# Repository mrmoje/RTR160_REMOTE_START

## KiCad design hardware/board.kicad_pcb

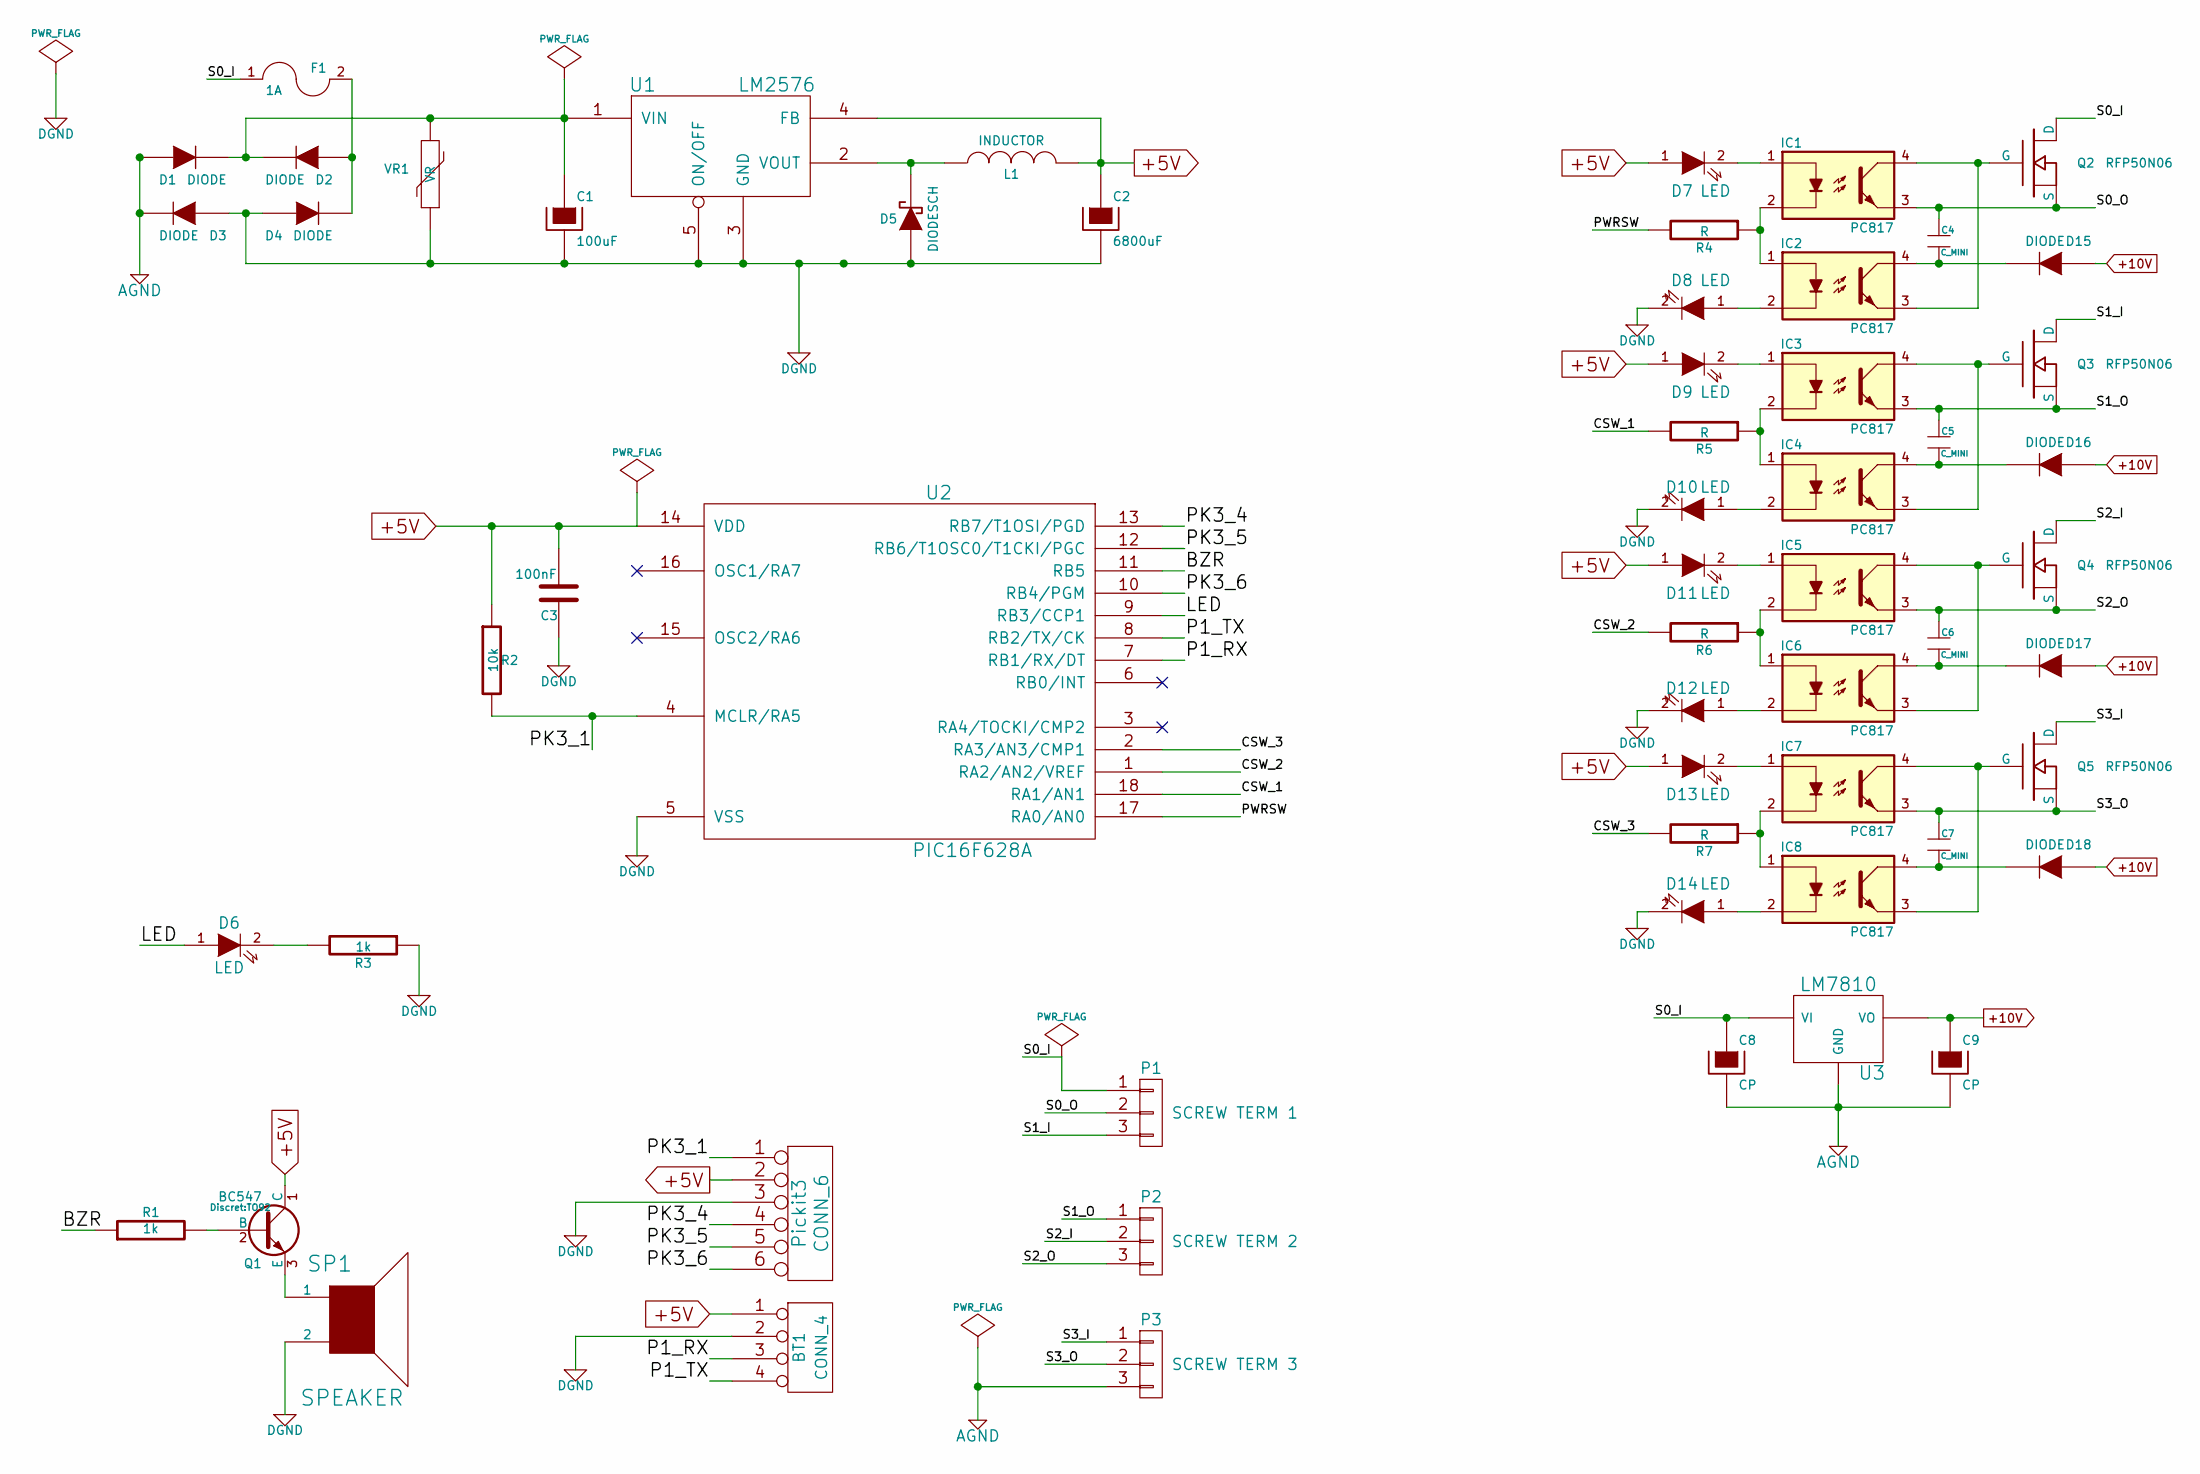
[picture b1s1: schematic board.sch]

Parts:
BT1: CONN_4; Pin_Header_Straight_1x04
C1: 100uF; Capacitor10x25RM2.5
C2: 6800uF; Capacitor16x25RM7.5
C3: 100nF; Capacitor7.5MMDiscRM5
C4, C5, C6, C7: C_MINI; Capacitor5x11RM2.5
C8, C9: CP; Capacitor8x13RM3.8
D1, D2, D3, D4, D15, D16, D17, D18: DIODE; Diode_DO-35_SOD27_Horizontal_RM10
D5: DIODESCH; Diode_DO-35_SOD27_Horizontal_RM10
D6, D7, D8, D9, D10, D11, D12, D13, D14: LED; LED-5MM
F1: 1A; Fuseholder5x20_horiz_SemiClosed_Casing10x25mm
IC1, IC2, IC3, IC4, IC5, IC6, IC7, IC8: PC817; DIP-4__300
L1: INDUCTOR; INDUCTOR_V
P1: SCREW TERM 1; bornier3
P2: SCREW TERM 2; bornier3
P3: SCREW TERM 3; bornier3
Pickit3: CONN_6; Pin_Header_Straight_1x06
Q1: BC547; TO92
Q2, Q3, Q4, Q5: RFP50N06; TO-220_FET-GDS_Vertical_LargePads
R1, R3: 1k; Resistor_Vertical_RM5mm
R2: 10k; Resistor_Vertical_RM5mm
R4, R5, R6, R7: R; Resistor_Horizontal_RM20mm
SP1: SPEAKER; MagneticBuzzer_ProSignal_ABI-009-RC
U1: LM2576; WAGO_734_5pin_Straight_RuggedPads
U2: PIC16F628A; DIP-18__300_ELL
U3: LM7810; 78XX
VR1: VR; Capacitor12MMDiscRM7.75

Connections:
+5V: BT1.1, C2.1, C3.2, D7.1 (A), D9.1 (A), D11.1 (A), D13.1 (A), L1.2, Pickit3.2, Q1.1 (C), R2.1, U1.4 (FB), U2.14 (VDD)
+10V: C9.1, D15.1 (A), D16.1 (A), D17.1 (A), D18.1 (A), U3.VO
/BZR: R1.1, U2.11 (RB5)
/CSW_1: R5.2, U2.18 (RA1/AN1)
/CSW_2: R6.2, U2.1 (RA2/AN2/VREF)
/CSW_3: R7.2, U2.2 (RA3/AN3/CMP1)
/LED: D6.1 (A), U2.9 (RB3/CCP1)
/P1_RX: BT1.3, U2.7 (RB1/RX/DT)
/P1_TX: BT1.4, U2.8 (RB2/TX/CK)
/PK3_1: Pickit3.1, R2.2, U2.4 (MCLR/RA5)
/PK3_4: Pickit3.4, U2.13 (RB7/T1OSI/PGD)
/PK3_5: Pickit3.5, U2.12 (RB6/T1OSC0/T1CKI/PGC)
/PK3_6: Pickit3.6, U2.10 (RB4/PGM)
/PWRSW: R4.2, U2.17 (RA0/AN0)
/S0_I: C8.1, F1.1, P1.1, Q2.D, U3.VI
/S0_O: C4.1 (A), IC1.3, P1.2, Q2.S
/S1_I: P1.3, Q3.D
/S1_O: C5.1 (A), IC3.3, P2.1, Q3.S
/S2_I: P2.2, Q4.D
/S2_O: C6.1 (A), IC5.3, P2.3, Q4.S
/S3_I: P3.1, Q5.D
/S3_O: C7.1 (A), IC7.3, P3.2, Q5.S
AGND: C8.2, C9.2, D1.1 (A), D3.2 (K), P3.3, U3.GND
DGND: BT1.2, C1.2, C2.2, C3.1, D3.1 (A), D4.1 (A), D5.1 (A), D8.2 (K), D10.2 (K), D12.2 (K), D14.2 (K), Pickit3.3, R3.1, SP1.2, U1.3 (GND), U1.5 (ON/OFF), U2.5 (VSS), VR1.1
unnamed: C1.1, D1.2 (K), D2.2 (K), U1.1 (VIN), VR1.2
unnamed: C4.2 (B), D15.2 (K), IC2.4
unnamed: C5.2 (B), D16.2 (K), IC4.4
unnamed: C6.2 (B), D17.2 (K), IC6.4
unnamed: C7.2 (B), D18.2 (K), IC8.4
unnamed: D2.1 (A), D4.2 (K), F1.2
unnamed: D5.2 (K), L1.1, U1.2 (VOUT)
unnamed: D6.2 (K), R3.2
unnamed: D7.2 (K), IC1.1
unnamed: D8.1 (A), IC2.2
unnamed: D9.2 (K), IC3.1
unnamed: D10.1 (A), IC4.2
unnamed: D11.2 (K), IC5.1
unnamed: D12.1 (A), IC6.2
unnamed: D13.2 (K), IC7.1
unnamed: D14.1 (A), IC8.2
unnamed: IC1.2, IC2.1, R4.1
unnamed: IC1.4, IC2.3, Q2.G
unnamed: IC3.2, IC4.1, R5.1
unnamed: IC3.4, IC4.3, Q3.G
unnamed: IC5.2, IC6.1, R6.1
unnamed: IC5.4, IC6.3, Q4.G
unnamed: IC7.2, IC8.1, R7.1
unnamed: IC7.4, IC8.3, Q5.G
unnamed: Q1.2 (B), R1.2
unnamed: Q1.3 (E), SP1.1

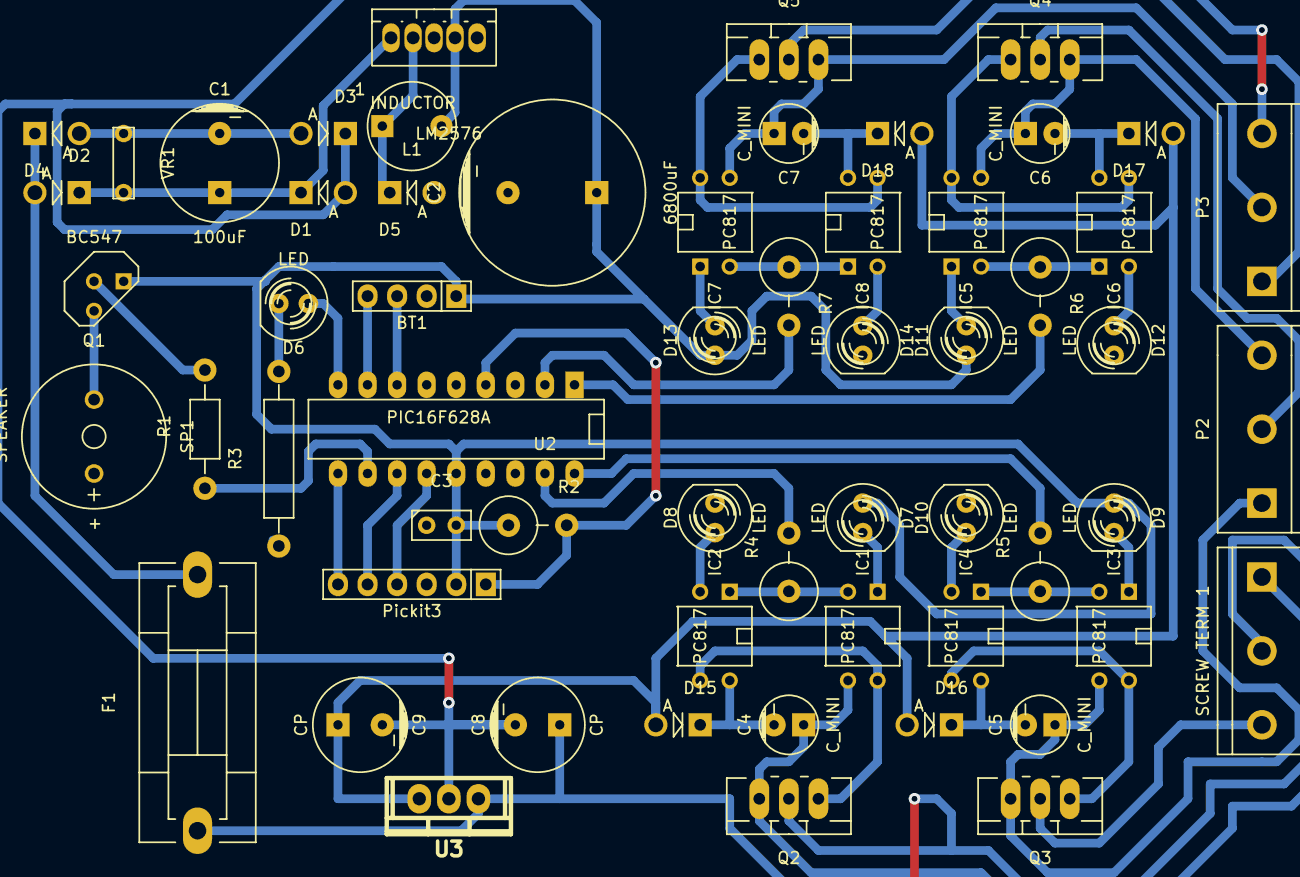
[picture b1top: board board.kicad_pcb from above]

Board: 2 copper layers, 59 parts (0 on the bottom side), 50 nets.

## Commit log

2014-10-18 Initial prototype. Works better on external power
    Suffers from brownouts and other power-related
    gotchas when powered from the bike.
2014-10-18 Replace LM7805 LVR with LM2576 Buck Converter
    Switched to a more efficient power supply plus add a large-ass capacitor
    to postpone brownouts during ignition.
    closes #1
    closes #3
2014-11-04 Refactor schema to include MOSFET & optocouplers
    Use N-channel MOSFETS for "high-side" switching
    Add optocouplers to isolate control & bike circuits
    10V LVR for bootstrap cap charge/power supply
    Purge mislabeled connector (P2 was mislabeled as Pickit 3 conn)
    Add screw terminal connectors
    (labeling/numbering is still incomplete)
2014-11-05 JZ: Label everything + ugly power tag workaround
2014-12-29 Heavily modded pcb + New footprint associations
2014-12-31 Forgot to connect power trace to uC & bt modules
    Discovered after second etch [facepalm]
